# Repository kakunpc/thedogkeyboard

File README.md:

# ビルドガイドは移動しました。

https://kakunpc.github.io/buildguides/thedogkeyboard

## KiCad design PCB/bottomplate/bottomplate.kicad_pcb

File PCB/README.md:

# わんわんわんキーボードロゴなしPCBデータ

## 作るために必要なもの

- [ダイオード　リードタイプ](https://yushakobo.jp/shop/a0800di-01-100/) x111
- [黄銅スペーサー（丸）M2  8mm](https://yushakobo.jp/shop/a0800c2/) x16
- [スリムヘッド小ねじ M2 3mmか4mm](https://yushakobo.jp/shop/a0800s2/) x32
- [ウレタンクッション – 丸型10mm 6個入り](https://yushakobo.jp/shop/a0800ur-01-6/) x1 (全部で6個)
- [タクタイルスイッチ – 3x6x4.3mm ブラケット付き](https://yushakobo.jp/shop/a1600ed-01-1/) x1
- [Pro Micro （コンスルー付き）](https://yushakobo.jp/shop/promicro-spring-pinheader/) x1
- [スタビライザー](https://shop.yushakobo.jp/collections/stabilizer/products/a0500st) 2Ux4 6.25Ux1 (基本的なレイアウトの場合)
- [MXキースイッチ](https://yushakobo.jp/product-category/switches/) x104～111個
- [MXキーキャップ](https://yushakobo.jp/product-category/keycaps/) x104～111個
- [USBケーブル Micro B 1m](https://yushakobo.jp/shop/usb_cable_micro_b/) x1

## オプション
- [フルカラーシリアルLED (WS2812B) 10個入り](https://yushakobo.jp/shop/a0800ws-01-10/) x12(全部で111個)
- [電子ワイヤー](https://akizukidenshi.com/catalog/g/gP-11640/) x1(ボトムとPCBをつなげるために使います)

## License
[MIT](https://github.com/kakunpc/thedogkeyboard/blob/master/LICENSE)

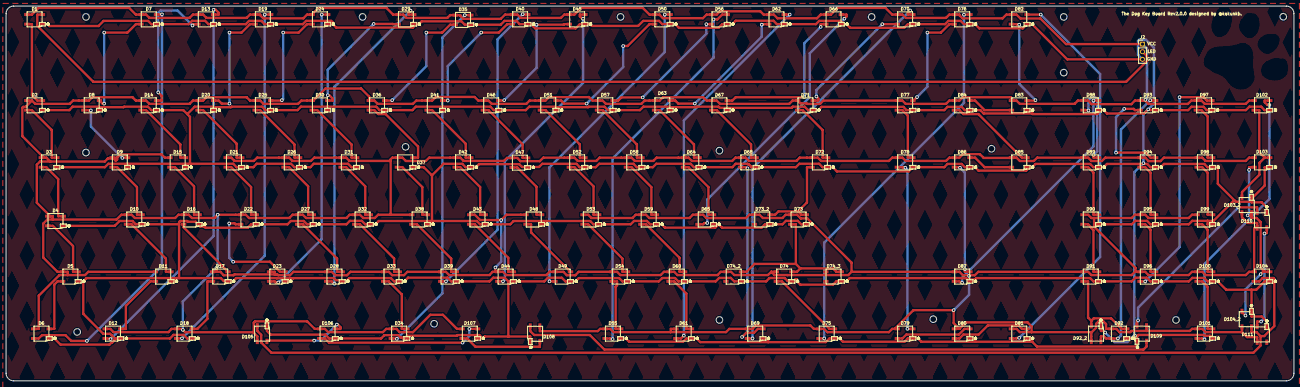
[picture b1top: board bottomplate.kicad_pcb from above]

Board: 2 copper layers, 429.9 x 125.1 mm, 134 parts (0 on the bottom side), 113 nets.

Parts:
D1, D2, D3, D4, D5, D6, D7, D8, D9, D10, D11, D12, D13, D14, D15, D16, D17, D18, D19, D20, D21, D22, D23, D24, D25, D26, D27, D28, D29, D30, D31, D32, D33, D34, D35, D36, D37, D38, D39, D40, D41, D42, D43, D44, D45, D46, D47, D48, D49, D50, D51, D52, D53, D54, D55, D56, D57, D58, D59, D60, D61, D62, D63, D64, D65, D66, D67, D68, D69, D70, D71, D72, D73, D73_2, D74, D74_2, D74_3, D75, D76, D77, D78, D79, D80, D81, D82, D83, D84, D85, D86, D87, D88, D89, D90, D91, D92, D92_2, D93, D94, D95, D96, D97, D98, D99, D100, D101, D102, D103, D103_2, D104, D104_2, D105, D106, D107, D108, D109, D110, D111: WS2812B
H1, H2, H3, H4, H5, H6, H7, H8, H9, H10, H11, H12, H13, H14, H15, H16: MountingHole; MountingHole_2.2mm_M2
J2: Conn_01x03_Female; PinHeader_1x03_P2.54mm_Vertical

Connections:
/LED: D1.4, J2.2
GND: D1.3, D2.3, D3.3, D4.3, D5.3, D6.3, D7.3, D8.3, D9.3, D10.3, D11.3, D12.3, D13.3, D14.3, D15.3, D16.3, D17.3, D18.3, D19.3, D20.3, D21.3, D22.3, D23.3, D24.3, D25.3, D26.3, D27.3, D28.3, D29.3, D30.3, D31.3, D32.3, D33.3, D34.3, D35.3, D36.3, D37.3, D38.3, D39.3, D40.3, D41.3, D42.3, D43.3, D44.3, D45.3, D46.3, D47.3, D48.3, D49.3, D50.3, D51.3, D52.3, D53.3, D54.3, D55.3, D56.3, D57.3, D58.3, D59.3, D60.3, D61.3, D62.3, D63.3, D64.3, D65.3, D66.3, D67.3, D68.3, D69.3, D70.3, D71.3, D72.3, D73.3, D73_2.3, D74.3, D74_2.3, D74_3.3, D75.3, D76.3, D77.3, D78.3, D79.3, D80.3, D81.3, D82.3, D83.3, D84.3, D85.3, D86.3, D87.3, D88.3, D89.3, D90.3, D91.3, D92.3, D92_2.3, D93.3, D94.3, D95.3, D96.3, D97.3, D98.3, D99.3, D100.3, D101.3, D102.3, D103.3, D103_2.3, D104.3, D104_2.3, D105.3, D106.3, D107.3, D108.3, D109.3, D110.3, D111.3, J2.3
unnamed: D1.2, D2.4
unnamed: D2.2, D3.4
unnamed: D3.2, D4.4
unnamed: D4.2, D5.4
unnamed: D5.2, D6.4
unnamed: D6.2, D7.4
unnamed: D7.2, D8.4
unnamed: D8.2, D9.4
unnamed: D10.2, D11.4
unnamed: D9.2, D10.4
unnamed: D11.2, D12.4
unnamed: D12.2, D13.4
unnamed: D13.2, D14.4
unnamed: D14.2, D15.4
unnamed: D15.2, D16.4
unnamed: D16.2, D17.4
unnamed: D17.2, D18.4
unnamed: D18.2, D19.4
unnamed: D19.2, D20.4
unnamed: D20.2, D21.4
unnamed: D21.2, D22.4
unnamed: D22.2, D23.4
unnamed: D23.2, D24.4
unnamed: D24.2, D25.4
unnamed: D25.2, D26.4
unnamed: D26.2, D27.4
unnamed: D27.2, D28.4
unnamed: D28.2, D29.4
unnamed: D29.2, D30.4
unnamed: D30.2, D31.4
unnamed: D31.2, D32.4
unnamed: D32.2, D33.4
unnamed: D33.2, D34.4
unnamed: D34.2, D35.4
unnamed: D35.2, D36.4
unnamed: D36.2, D37.4
unnamed: D37.2, D38.4
unnamed: D38.2, D39.4
unnamed: D39.2, D40.4
unnamed: D40.2, D41.4
unnamed: D41.2, D42.4
unnamed: D42.2, D43.4
unnamed: D43.2, D44.4
unnamed: D44.2, D45.4
unnamed: D45.2, D46.4
unnamed: D46.2, D47.4
unnamed: D47.2, D48.4
unnamed: D48.2, D49.4
unnamed: D49.2, D50.4
unnamed: D50.2, D51.4
unnamed: D51.2, D52.4
unnamed: D52.2, D53.4
unnamed: D53.2, D54.4
unnamed: D54.2, D55.4
unnamed: D55.2, D56.4
unnamed: D56.2, D57.4
unnamed: D57.2, D58.4
unnamed: D58.2, D59.4
unnamed: D59.2, D60.4
unnamed: D60.2, D61.4
unnamed: D61.2, D62.4
unnamed: D62.2, D63.4
unnamed: D63.2, D64.4
unnamed: D64.2, D65.4
unnamed: D65.2, D66.4
unnamed: D66.2, D67.4
unnamed: D67.2, D68.4
unnamed: D68.2, D69.4
unnamed: D69.2, D70.4
unnamed: D70.2, D71.4
unnamed: D71.2, D72.4
unnamed: D72.2, D73.4, D73_2.4
unnamed: D73.2, D74.4, D74_2.4, D74_3.4
unnamed: D74.2, D75.4
unnamed: D75.2, D76.4
unnamed: D76.2, D77.4
unnamed: D77.2, D78.4
unnamed: D78.2, D79.4
unnamed: D79.2, D80.4
unnamed: D80.2, D81.4
unnamed: D81.2, D82.4
unnamed: D82.2, D83.4
unnamed: D83.2, D84.4
unnamed: D84.2, D85.4
unnamed: D85.2, D86.4
unnamed: D86.2, D87.4
unnamed: D87.2, D88.4
unnamed: D88.2, D89.4
unnamed: D89.2, D90.4
unnamed: D90.2, D91.4
unnamed: D91.2, D92.4, D92_2.4
unnamed: D92.2, D92_2.2, D93.4
unnamed: D93.2, D94.4
unnamed: D94.2, D95.4
unnamed: D95.2, D96.4
unnamed: D96.2, D97.4
unnamed: D97.2, D98.4
unnamed: D98.2, D99.4
unnamed: D100.2, D101.4
unnamed: D99.2, D100.4
unnamed: D101.2, D102.4
unnamed: D102.2, D103.4, D103_2.4
unnamed: D103.2, D103_2.2, D104.4, D104_2.4
unnamed: D104.2, D104_2.2, D105.4
unnamed: D105.2, D106.4
unnamed: D106.2, D107.4
unnamed: D107.2, D108.4
unnamed: D108.2, D109.4
unnamed: D109.2, D110.4
unnamed: D110.2, D111.4
VCC: D1.1, D2.1, D3.1, D4.1, D5.1, D6.1, D7.1, D8.1, D9.1, D10.1, D11.1, D12.1, D13.1, D14.1, D15.1, D16.1, D17.1, D18.1, D19.1, D20.1, D21.1, D22.1, D23.1, D24.1, D25.1, D26.1, D27.1, D28.1, D29.1, D30.1, D31.1, D32.1, D33.1, D34.1, D35.1, D36.1, D37.1, D38.1, D39.1, D40.1, D41.1, D42.1, D43.1, D44.1, D45.1, D46.1, D47.1, D48.1, D49.1, D50.1, D51.1, D52.1, D53.1, D54.1, D55.1, D56.1, D57.1, D58.1, D59.1, D60.1, D61.1, D62.1, D63.1, D64.1, D65.1, D66.1, D67.1, D68.1, D69.1, D70.1, D71.1, D72.1, D73.1, D73_2.1, D74.1, D74_2.1, D74_3.1, D75.1, D76.1, D77.1, D78.1, D79.1, D80.1, D81.1, D82.1, D83.1, D84.1, D85.1, D86.1, D87.1, D88.1, D89.1, D90.1, D91.1, D92.1, D92_2.1, D93.1, D94.1, D95.1, D96.1, D97.1, D98.1, D99.1, D100.1, D101.1, D102.1, D103.1, D103_2.1, D104.1, D104_2.1, D105.1, D106.1, D107.1, D108.1, D109.1, D110.1, D111.1, J2.1

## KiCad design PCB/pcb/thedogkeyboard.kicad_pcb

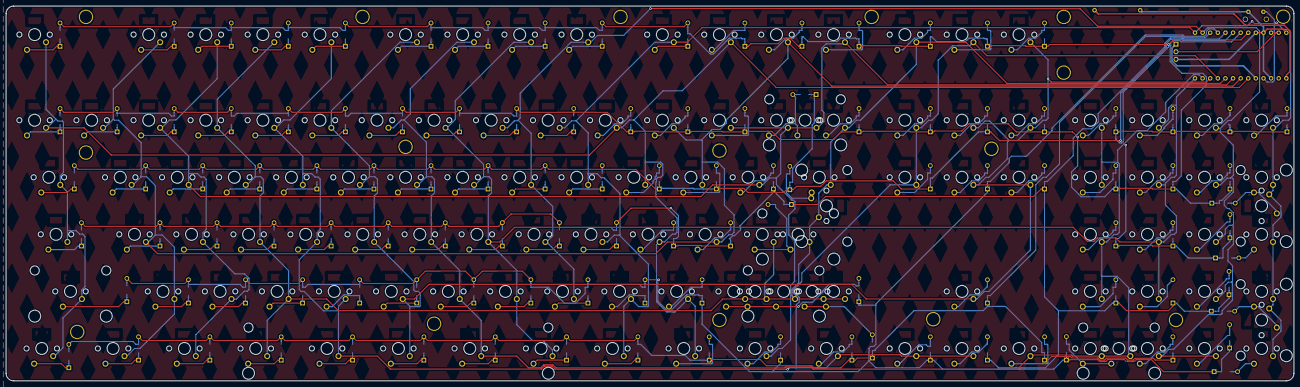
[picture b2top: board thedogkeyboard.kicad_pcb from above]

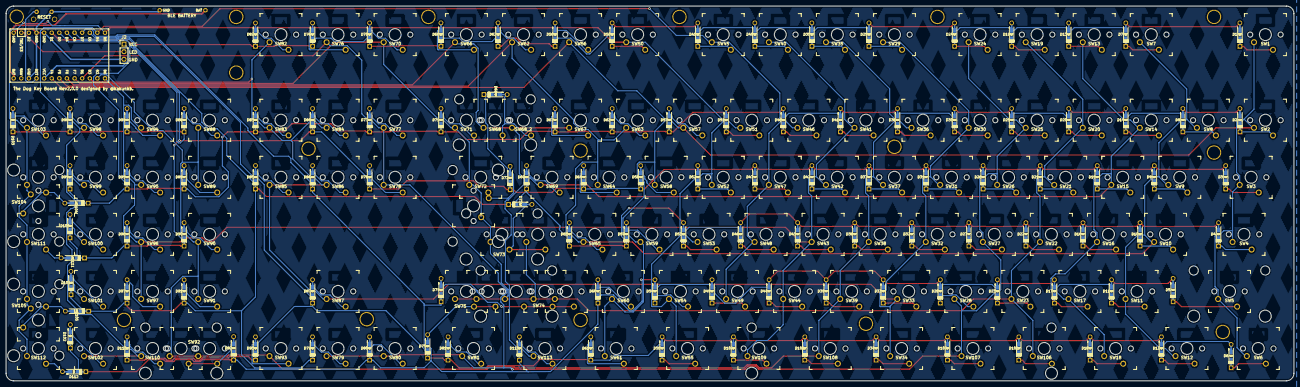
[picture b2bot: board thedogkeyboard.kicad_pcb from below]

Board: 2 copper layers, 429.9 x 125.1 mm, 255 parts (114 on the bottom side), 134 nets.

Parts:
BAT1: BLE_BAT; BLEMicroPro_Bat
D1, D2, D3, D4, D5, D6, D7, D8, D9, D10, D11, D12, D13, D14, D15, D16, D17, D18, D19, D20, D21, D22, D23, D24, D25, D26, D27, D28, D29, D30, D31, D32, D33, D34, D35, D36, D37, D38, D39, D40, D41, D42, D43, D44, D45, D46, D47, D48, D49, D50, D51, D52, D53, D54, D55, D56, D57, D58, D59, D60, D61, D62, D63, D64, D65, D66, D67, D68, D69, D70, D71, D72, D73, D74, D75, D76, D77, D78, D79, D80, D81, D82, D83, D84, D85, D86, D87, D88, D89, D90, D91, D92, D93, D94, D95, D96, D97, D98, D99, D100, D101, D102, D103, D104, D105, D106, D107, D108, D109, D110, D111, D112, D113: D; Diode
H1, H2, H3, H4, H5, H6, H7, H8, H9, H10, H11, H12, H13, H14, H15, H16: MountingHole; SPACER_HOLE
J2: Conn_01x03_Female; PinHeader_1x03_P2.54mm_Vertical
RESET1: SW_PUSH; TSZJ36H
SW1, SW2, SW7, SW8, SW9, SW10, SW11, SW13, SW14, SW15, SW16, SW17, SW19, SW20, SW21, SW22, SW23, SW24, SW25, SW26, SW27, SW28, SW29, SW30, SW31, SW32, SW33, SW35, SW36, SW37, SW38, SW39, SW40, SW41, SW42, SW43, SW44, SW45, SW46, SW47, SW48, SW49, SW50, SW51, SW52, SW53, SW54, SW56, SW57, SW58, SW59, SW60, SW62, SW63, SW64, SW65, SW66, SW67, SW68_2, SW70, SW71, SW73_2, SW74_2, SW74_3, SW75_2, SW75_3, SW76, SW77, SW78, SW79, SW80, SW82, SW83, SW84, SW85, SW86, SW87, SW88, SW89, SW90, SW91, SW92_2, SW93, SW94, SW95, SW96, SW97, SW98, SW99, SW100, SW101, SW102, SW103, SW104_1, SW105_2, SW110, SW111, SW112: SW_PUSH; Mx100H
SW3, SW72: SW_PUSH; Mx150H
SW4: SW_PUSH; Mx175H
SW5, SW73: SW_PUSH; Mx225H
SW6, SW12, SW18, SW55, SW61, SW69, SW81, SW106, SW107, SW108, SW109, SW113: SW_PUSH; Mx125H
SW34: SW_PUSH; Mx625H
SW68, SW92: SW_PUSH; Mx200H
SW72_2, SW104, SW105: SW_PUSH; Mx200V
SW74: SW_PUSH; Mx275H
U1: ProMicro; ArduinoBLEMicroPro_BSilik_ConSuru

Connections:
/LED: J2.2, U1.1
/RST: RESET1.2, U1.22
/col0: SW1.1, SW2.1, SW3.1, SW4.1, SW5.1, SW6.1, SW56.1, SW57.1, SW58.1, SW59.1, SW60.1, SW61.1, U1.20
/col1: SW7.1, SW8.1, SW9.1, SW10.1, SW11.1, SW12.1, SW62.1, SW63.1, SW64.1, SW65.1, U1.19
/col2: SW13.1, SW14.1, SW15.1, SW16.1, SW17.1, SW18.1, SW66.1, SW67.1, SW68.1, SW68_2.1, SW69.1, SW113.1, U1.18
/col3: SW19.1, SW20.1, SW21.1, SW22.1, SW23.1, SW70.1, SW71.1, SW72.1, SW72_2.1, SW73.1, SW73_2.1, SW74.1, SW74_2.1, SW74_3.1, SW75_2.1, SW75_3.1, SW106.1, U1.17
/col4: SW24.1, SW25.1, SW26.1, SW27.1, SW28.1, SW76.1, SW77.1, SW78.1, SW79.1, SW80.1, SW81.1, SW107.1, U1.16
/col5: SW29.1, SW30.1, SW31.1, SW32.1, SW33.1, SW34.1, SW82.1, SW83.1, SW84.1, SW85.1, SW86.1, SW87.1, U1.15
/col6: SW35.1, SW36.1, SW37.1, SW38.1, SW39.1, SW88.1, SW89.1, SW90.1, SW91.1, SW92.1, SW92_2.1, SW93.1, SW108.1, U1.14
/col7: SW40.1, SW41.1, SW42.1, SW43.1, SW44.1, SW94.1, SW95.1, SW96.1, SW97.1, SW109.1, U1.13
/col8: SW45.1, SW46.1, SW47.1, SW48.1, SW49.1, SW98.1, SW99.1, SW100.1, SW101.1, SW102.1, SW110.1, U1.11
/col9: SW50.1, SW51.1, SW52.1, SW53.1, SW54.1, SW55.1, SW103.1, SW104.1, SW104_1.1, SW105.1, SW105_2.1, SW111.1, SW112.1, U1.12
/row0: D1.2, D7.2, D13.2, D19.2, D24.2, D29.2, D35.2, D40.2, D45.2, D50.2, D56.1, D62.1, D66.1, D70.1, D76.1, D82.1, D88.1, D94.1, D98.1, D103.1, U1.5
/row1: D2.2, D8.2, D14.2, D20.2, D25.2, D30.2, D36.2, D41.2, D46.2, D51.2, D57.1, D63.1, D67.1, D71.1, D77.1, D83.1, D89.1, D95.1, D99.1, D104.1, U1.6
/row2: D3.2, D9.2, D15.2, D21.2, D26.2, D31.2, D37.2, D42.2, D47.2, D52.2, D58.1, D64.1, D68.1, D72.1, D78.1, D84.1, D90.1, D96.1, D100.1, D111.1, U1.7
/row3: D4.2, D10.2, D16.2, D22.2, D27.2, D32.2, D38.2, D43.2, D48.2, D53.2, D59.1, D65.1, D69.1, D73.1, D79.1, D85.1, D91.1, D97.1, D101.1, D105.1, U1.8
/row4: D5.2, D11.2, D17.2, D23.2, D28.2, D33.2, D39.2, D44.2, D49.2, D54.2, D60.1, D74.1, D80.1, D86.1, D92.1, D102.1, D112.1, D113.1, U1.9
/row5: D6.2, D12.2, D18.2, D34.2, D55.2, D61.1, D75.1, D81.1, D87.1, D93.1, D106.2, D107.2, D108.2, D109.2, D110.1, U1.10
BAT: BAT1.2, U1.26
GND: BAT1.1, J2.3, RESET1.1, U1.3, U1.4, U1.23, U1.25
unnamed: D1.1, SW1.2
unnamed: D2.1, SW2.2
unnamed: D3.1, SW3.2
unnamed: D4.1, SW4.2
unnamed: D5.1, SW5.2
unnamed: D6.1, SW6.2
unnamed: D7.1, SW7.2
unnamed: D8.1, SW8.2
unnamed: D9.1, SW9.2
unnamed: D10.1, SW10.2
unnamed: D11.1, SW11.2
unnamed: D12.1, SW12.2
unnamed: D13.1, SW13.2
unnamed: D14.1, SW14.2
unnamed: D15.1, SW15.2
unnamed: D16.1, SW16.2
unnamed: D17.1, SW17.2
unnamed: D18.1, SW18.2
unnamed: D19.1, SW19.2
unnamed: D20.1, SW20.2
unnamed: D21.1, SW21.2
unnamed: D22.1, SW22.2
unnamed: D23.1, SW23.2
unnamed: D24.1, SW24.2
unnamed: D25.1, SW25.2
unnamed: D26.1, SW26.2
unnamed: D27.1, SW27.2
unnamed: D28.1, SW28.2
unnamed: D29.1, SW29.2
unnamed: D30.1, SW30.2
unnamed: D31.1, SW31.2
unnamed: D32.1, SW32.2
unnamed: D33.1, SW33.2
unnamed: D34.1, SW34.2
unnamed: D35.1, SW35.2
unnamed: D36.1, SW36.2
unnamed: D37.1, SW37.2
unnamed: D38.1, SW38.2
unnamed: D39.1, SW39.2
unnamed: D40.1, SW40.2
unnamed: D41.1, SW41.2
unnamed: D42.1, SW42.2
unnamed: D43.1, SW43.2
unnamed: D44.1, SW44.2
unnamed: D45.1, SW45.2
unnamed: D46.1, SW46.2
unnamed: D47.1, SW47.2
unnamed: D48.1, SW48.2
unnamed: D49.1, SW49.2
unnamed: D50.1, SW50.2
unnamed: D51.1, SW51.2
unnamed: D52.1, SW52.2
unnamed: D53.1, SW53.2
unnamed: D54.1, SW54.2
unnamed: D55.1, SW55.2
unnamed: D56.2, SW56.2
unnamed: D57.2, SW57.2
unnamed: D58.2, SW58.2
unnamed: D59.2, SW59.2
unnamed: D60.2, SW60.2
unnamed: D61.2, SW61.2
unnamed: D62.2, SW62.2
unnamed: D63.2, SW63.2
unnamed: D64.2, SW64.2
unnamed: D65.2, SW65.2
unnamed: D66.2, SW66.2
unnamed: D67.2, SW67.2
unnamed: D68.2, SW68.2, SW68_2.2
unnamed: D69.2, SW69.2
unnamed: D70.2, SW70.2
unnamed: D71.2, SW71.2
unnamed: D72.2, SW72.2, SW72_2.2
unnamed: D73.2, SW73.2, SW73_2.2
unnamed: D74.2, SW74.2, SW74_2.2, SW74_3.2
unnamed: D75.2, SW75_2.2, SW75_3.2
unnamed: D76.2, SW76.2
unnamed: D77.2, SW77.2
unnamed: D78.2, SW78.2
unnamed: D79.2, SW79.2
unnamed: D80.2, SW80.2
unnamed: D81.2, SW81.2
unnamed: D82.2, SW82.2
unnamed: D83.2, SW83.2
unnamed: D84.2, SW84.2
unnamed: D85.2, SW85.2
unnamed: D86.2, SW86.2
unnamed: D87.2, SW87.2
unnamed: D88.2, SW88.2
unnamed: D89.2, SW89.2
unnamed: D90.2, SW90.2
unnamed: D91.2, SW91.2
unnamed: D92.2, SW92.2, SW92_2.2
unnamed: D93.2, SW93.2
unnamed: D94.2, SW94.2
unnamed: D95.2, SW95.2
unnamed: D96.2, SW96.2
unnamed: D97.2, SW97.2
unnamed: D98.2, SW98.2
unnamed: D99.2, SW99.2
unnamed: D100.2, SW100.2
unnamed: D101.2, SW101.2
unnamed: D102.2, SW102.2
unnamed: D103.2, SW103.2
unnamed: D104.2, SW104.2, SW104_1.2
unnamed: D105.2, SW105.2, SW105_2.2
unnamed: D106.1, SW106.2
unnamed: D107.1, SW107.2
unnamed: D108.1, SW108.2
unnamed: D109.1, SW109.2
unnamed: D110.2, SW110.2
unnamed: D111.2, SW111.2
unnamed: D112.2, SW112.2
unnamed: D113.2, SW113.2
VCC: J2.1, U1.21

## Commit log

2019-11-18 inport
2019-11-18 リンク修正
2020-01-29 干渉についての説明
2020-04-03 Bump kind-of from 6.0.2 to 6.0.3
    Bumps [kind-of](https://github.com/jonschlinkert/kind-of) from 6.0.2 to 6.0.3.
    - [Release notes](https://github.com/jonschlinkert/kind-of/releases)
    - [Changelog](https://github.com/jonschlinkert/kind-of/blob/master/CHANGELOG.md)
    - [Commits](https://github.com/jonschlinkert/kind-of/compare/6.0.2...6.0.3)
2020-07-18 Bump lodash from 4.17.15 to 4.17.19
    Bumps [lodash](https://github.com/lodash/lodash) from 4.17.15 to 4.17.19.
    - [Release notes](https://github.com/lodash/lodash/releases)
    - [Commits](https://github.com/lodash/lodash/compare/4.17.15...4.17.19)
2020-08-01 move
2021-02-16 add 2.0 pcb
2021-02-16 add readme
2021-02-16 fix license
